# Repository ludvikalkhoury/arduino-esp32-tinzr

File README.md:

# TinZr ESP32-C3 Arduino Board Manager Package

This repository contains the **TinZr**, an ESP32-C3-based custom board definition for the Arduino IDE.  
It provides a clean, Boards-Manager-installable package so anyone can use your board with one simple URL.

## Publication
The manuscript describing this work is available at: https://www.sciencedirect.com/science/article/pii/S246806722600101X.
It is also included in this repository (`TinZr_Manuscript.pdf`). 

Additionally, all production materials, including printed circuit board (PCB) design files, 3D-printable enclosure models, and component lists, are available at: https://zenodo.org/records/21892119

If you use this work, please cite:
> **Alkhoury, L.**, Moore, T., Swissler, P., Hill, N. J., Shah, S. A., & Kam, M. (2026). TinZr: A compact wireless ESP32-C3 platform for multi-modal physiological sensor integration and data acquisition. HardwareX, e00833.

---
## Pinout

## 🚀 Quick Install

### 1️⃣ Install Espressif ESP32
Open the Arduino IDE and go to:
- Go to **Tools → Board → Boards Manager**
- Find ``esp32 by Espressif Systems``
- Install *only* version `3.3.4`

**⚠️ IMPORTANT: This project is tested and supported exclusively with ESP32 core version `3.3.4`.**  
**Do NOT use any other version — builds may fail or behave incorrectly.**

### 2️⃣ Add the Boards Manager URL
Open the Arduino IDE and go to:

**File → Preferences → Additional Boards Manager URLs**, then paste:

```
https://ludvikalkhoury.github.io/TinZr/package_tinzr_index.json
```

Click **OK**.

### 3️⃣ Install the board package
In Arduino IDE:
- Go to **Tools → Board → Boards Manager**
- Search for **TinZr**
- Click **Install**

### 4️⃣ Select your board
Go to:

**Tools → Board → TinZr Boards → TinZr ESP32-C3 Rev5**

### 5️⃣ Install `TinZrConnect` as a Zipped Arduino Library
#### A) Create the ZIP (IMPORTANT: zip the *library folder*, not the whole TinZr repo)
- Navigate to the `libraries` directory. There you will find the `TinZrConnect` folder (the one that contains `library.properties`).
- Create a zipped version of the `TinZrConnect` folder, and name it `TinZrConnect.zip`.

#### B) Install the ZIP in Arduino IDE
1. In Arduino IDE, go to:
   - **Sketch → Include Library → Add .ZIP Library…**
2. Select `TinZrConnect.zip`
3. Wait for the confirmation message (bottom status bar).

#### C) Verify Installation
1. Go to:
   - **File → Examples**
2. Scroll to find:
   - **TinZrConnect**
3. Open an example sketch and compile.

If you see the examples and the sketch compiles, the library is installed correctly ✅

## 💡 Example Sketch (NeoPixel Test)

```cpp
#include <Arduino.h>
#include "TinZrCore.h" // this library declares TinZrCore TinZr
#include "TinZrLED.h"  // this library declares TinZrStatusLED TinZrLED

void setup() {
    TinZr.begin(25); //LED brightness is 25
}

void loop() {
    TinZrLED.setColor(255,0,0); delay(500);
    TinZrLED.setColor(0,255,0); delay(500);
    TinZrLED.setColor(0,0,255); delay(500);
}
```

#

Copyright © 2026 Ludvik Alkhoury

This software is licensed under the GNU General Public License v3.0.
Commercial licensing options are available upon request.

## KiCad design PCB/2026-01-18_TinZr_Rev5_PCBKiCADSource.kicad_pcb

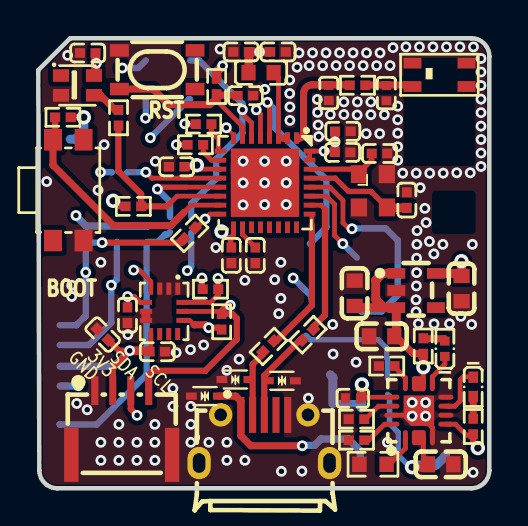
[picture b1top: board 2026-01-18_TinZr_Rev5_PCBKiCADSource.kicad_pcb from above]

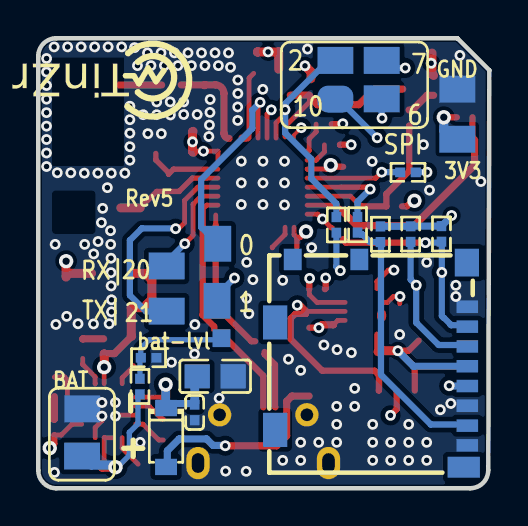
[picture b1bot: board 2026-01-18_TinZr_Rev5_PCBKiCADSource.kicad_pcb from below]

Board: 4 copper layers, 25.1 x 25.0 mm, 68 parts (12 on the bottom side), 42 nets.

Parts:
ANT2: ANT-SMD_4P-L3.2-W1.6
C3, C4, C5, C6, C7, C8, C9, C10, C11, C12, C14, C24, C25, C26, C28: c0402
C16, C31, C34: C0402
C18: C0805
C21, C27, C29, C33: C0603
CN1: CONN-SMD_1.0T-4P
D1: SOD-123_L2.7-W1.6-LS3.7-RD
L4: L0603
LED3: LED-SMD_4P-L2.0-W2.0-TL_WS2812B-2020
LED5: LED0402-RD_GREEN
R11, R19, R20, R25, R26, R27, R58, R61: r0402
R17: R0603
R28, R29, R30, R31, R44, R48, R49, R50, R57, R59, R60, R62, R63, R64, R65, R66, R67: R0402
SIM1: SIM-SMD_8P-1040310811
SW2: KEY-SMD_4P-L4.2-W3.2-P2.20-LS4.6
U1: QFN-32_L5.0-W5.0-P0.50-TL-EP3.7
U4: CRYSTAL-SMD_4P-L2.0-W1.6-BL_7D026000M01
U12, U13, U14: SOD-523_L1.2-W0.8-LS1.6-BI
U16: SOT-23-5_L2.9-W1.6-P0.95-LS2.8-BR
U18: SW-SMD_E-SWITCH_TL1014AFXXX
U19: LGA-14_L3.0-W2.5-P0.50-TL
U22: LED0402-RD_YELLOW
U23: QFN-16_L3.0-W3.0-P0.50-TL-EP1.7
USB2: MICRO-USB-SMD_MICROXNJ_1

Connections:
$1N1048: L4.2, U1.2, U1.3
$1N1429: C7.2, U1.18
$1N2460: C31.2, R29.2, U1.1
$1N25832: D1.2, U12.2, USB2.1
$1N25847: R59.1, U13.2, USB2.2
$1N25849: R60.1, U14.2, USB2.3
$1N31251: ANT2.1, C34.2, R29.1
$1N47755: LED3.3, R28.2
$1N85064: R26.2, R50.1, SIM1.7
$1N94189: U22.1, U23.7
$1N94195: LED5.1, U23.9
$1N94200: R17.2, U23.1
$1N94207: R57.2, U23.14
$1N94553: R27.1, R48.2, SIM1.3
$1N94607: R49.1, SIM1.5
$1N94651: R25.2, R44.2, SIM1.2
$1N97194: R62.2, U1.9
$1N97235: R63.2, U1.10
$1N106267: LED5.2, R64.1
$1N106270: R65.1, U22.2
$1N126315: R66.2, U23.16
$1N126394: R67.2, U23.12
+3V3: C3.1, C4.2, C5.2, C6.2, C8.2, C9.2, C12.1, C21.2, C24.1, C25.1, C26.1, CN1.2, L4.1, LED3.4, R11.2, R19.2, R20.1, R25.1, R26.1, R27.2, R58.2, R61.2, SIM1.4, U1.11, U1.17, U1.31, U1.32, U16.5, U19.5, U19.8, U19.12
BAT+: C33.2, R30.2, U23.2, U23.3
BATTERY_V_LEVEL: R30.1, R31.2
BOOT/PB: R20.2, U1.15, U18.4
CHIP_EN: C14.2, R11.1, SW2.2, U1.7
D+: R60.2, U1.26
D-: R59.2, U1.25
GND: ANT2.2, ANT2.3, ANT2.4, C3.2, C4.1, C5.1, C6.1, C7.1, C8.1, C9.1, C10.2, C11.1, C12.2, C14.1, C16.1, C18.1, C21.1, C24.2, C25.2, C26.2, C27.1, C28.2, C29.1, C31.1, C33.1, C34.1, CN1.0, CN1.1, LED3.2, R17.1, R31.1, R57.1, R66.1, R67.1, SIM1.1, SIM1.6, SIM1.8, SW2.4, U1.33, U4.2, U4.4, U12.1, U13.1, U14.1, U16.2, U18.1, U19.1, U19.2, U19.3, U19.6, U19.7, U23.4, U23.6, U23.8, U23.15, U23.17, USB2.5, USB2.6, USB2.7, USB2.8, USB2.9
IMU_INT: U1.8, U19.4
POW: C27.2, C29.2, R64.2, R65.2, U16.1, U16.3, U23.5, U23.10, U23.11
RGB: R28.1, R58.1, U1.14
SCL: CN1.4, R61.1, R63.1, U19.13
SDA: CN1.3, R19.1, R62.1, U19.14
SD_CS: R44.1, U1.16
SPCLK: R49.2, U1.12
SPID/MOSI: R50.2, U1.13
SPIQ/MISO: R48.1, U1.6
VBUS: C16.2, C18.2, C28.1, D1.1, U23.13
XTAL_N: C10.1, U1.29, U4.3
XTAL_P: C11.2, U1.30, U4.1

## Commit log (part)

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2025-10-23 created zip! Ready for release.
2025-10-23 New zip
2025-10-23 Another new zip
2025-10-23 new zip again ...
2025-10-23 new hash
2025-10-23 Added main menu for the tools in Arduino
2025-10-23 updated the boards info and created new zip
2025-10-23 Added the docs to this repo
2025-10-23 Updated the preference link
2025-10-23 Added the first readme
2025-10-23 Update README with formatted content
2025-10-23 Update README with pinout and formatting fixes
    Added pinout information and updated formatting.
2025-10-24 Added example codes.
2025-10-24 WIP: first attempt for the GUI.
2025-10-27 Made some modifications to the GUI to modify the RGB LED on the board and show IMU and PPG data. Next I will add saving functionalities.
2025-10-27 some fixes
2025-10-27 Added pinout to docs.
